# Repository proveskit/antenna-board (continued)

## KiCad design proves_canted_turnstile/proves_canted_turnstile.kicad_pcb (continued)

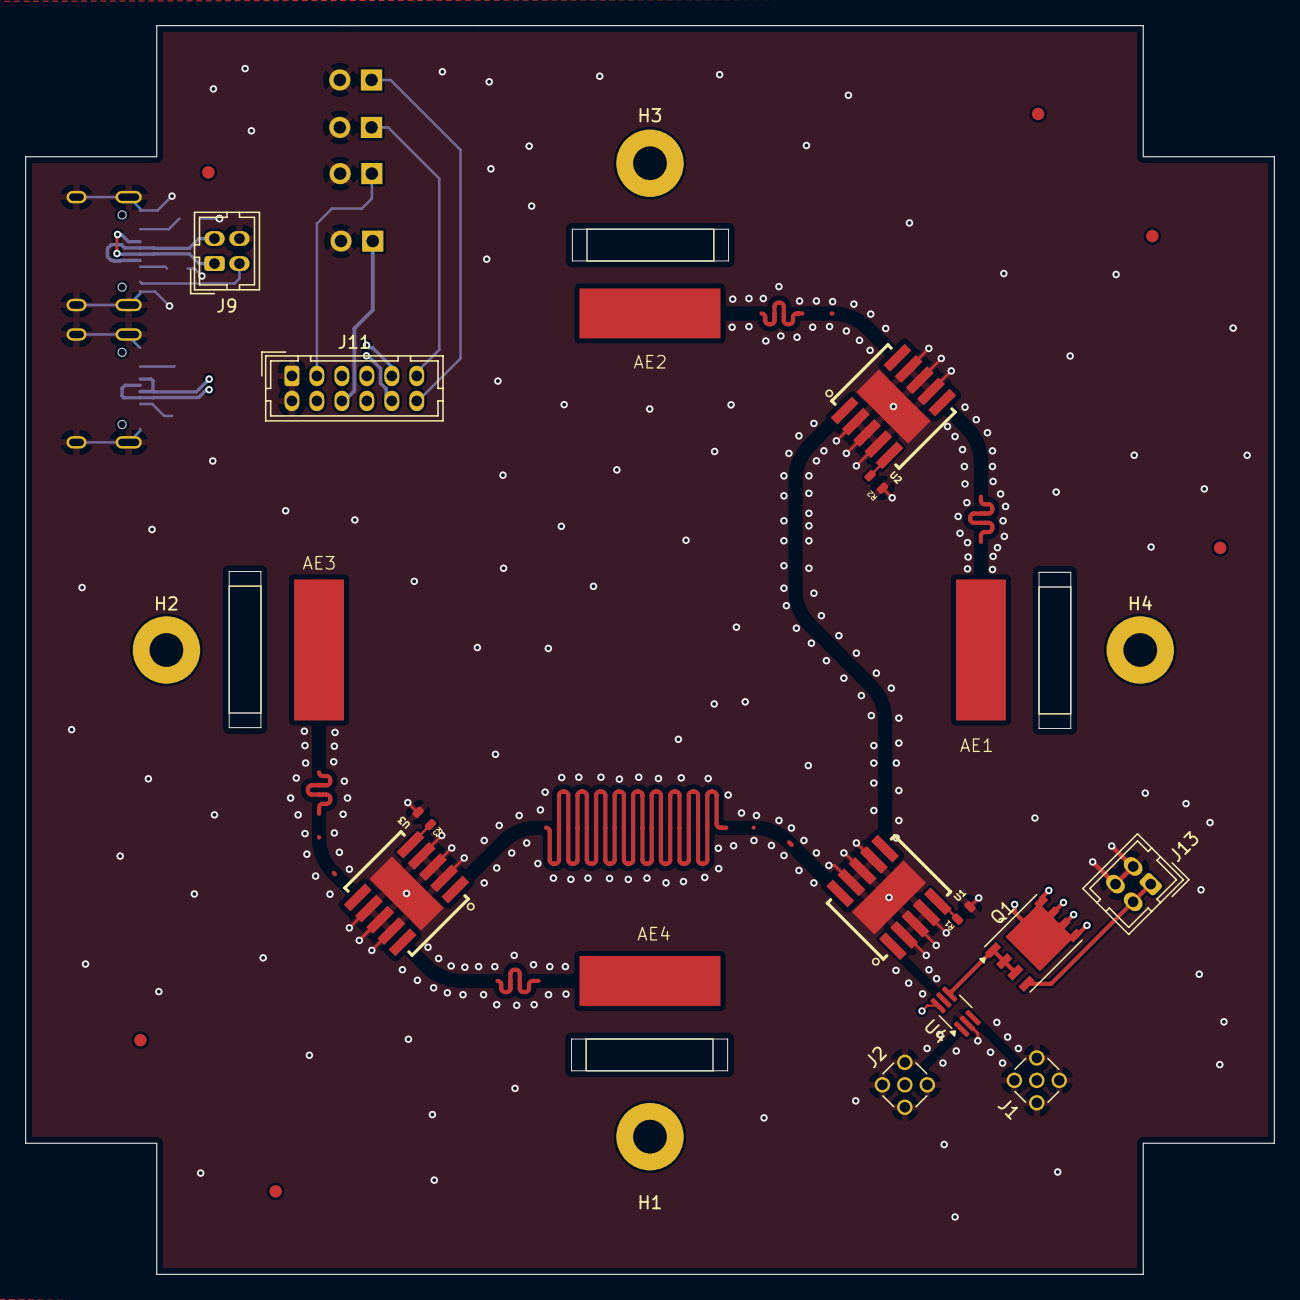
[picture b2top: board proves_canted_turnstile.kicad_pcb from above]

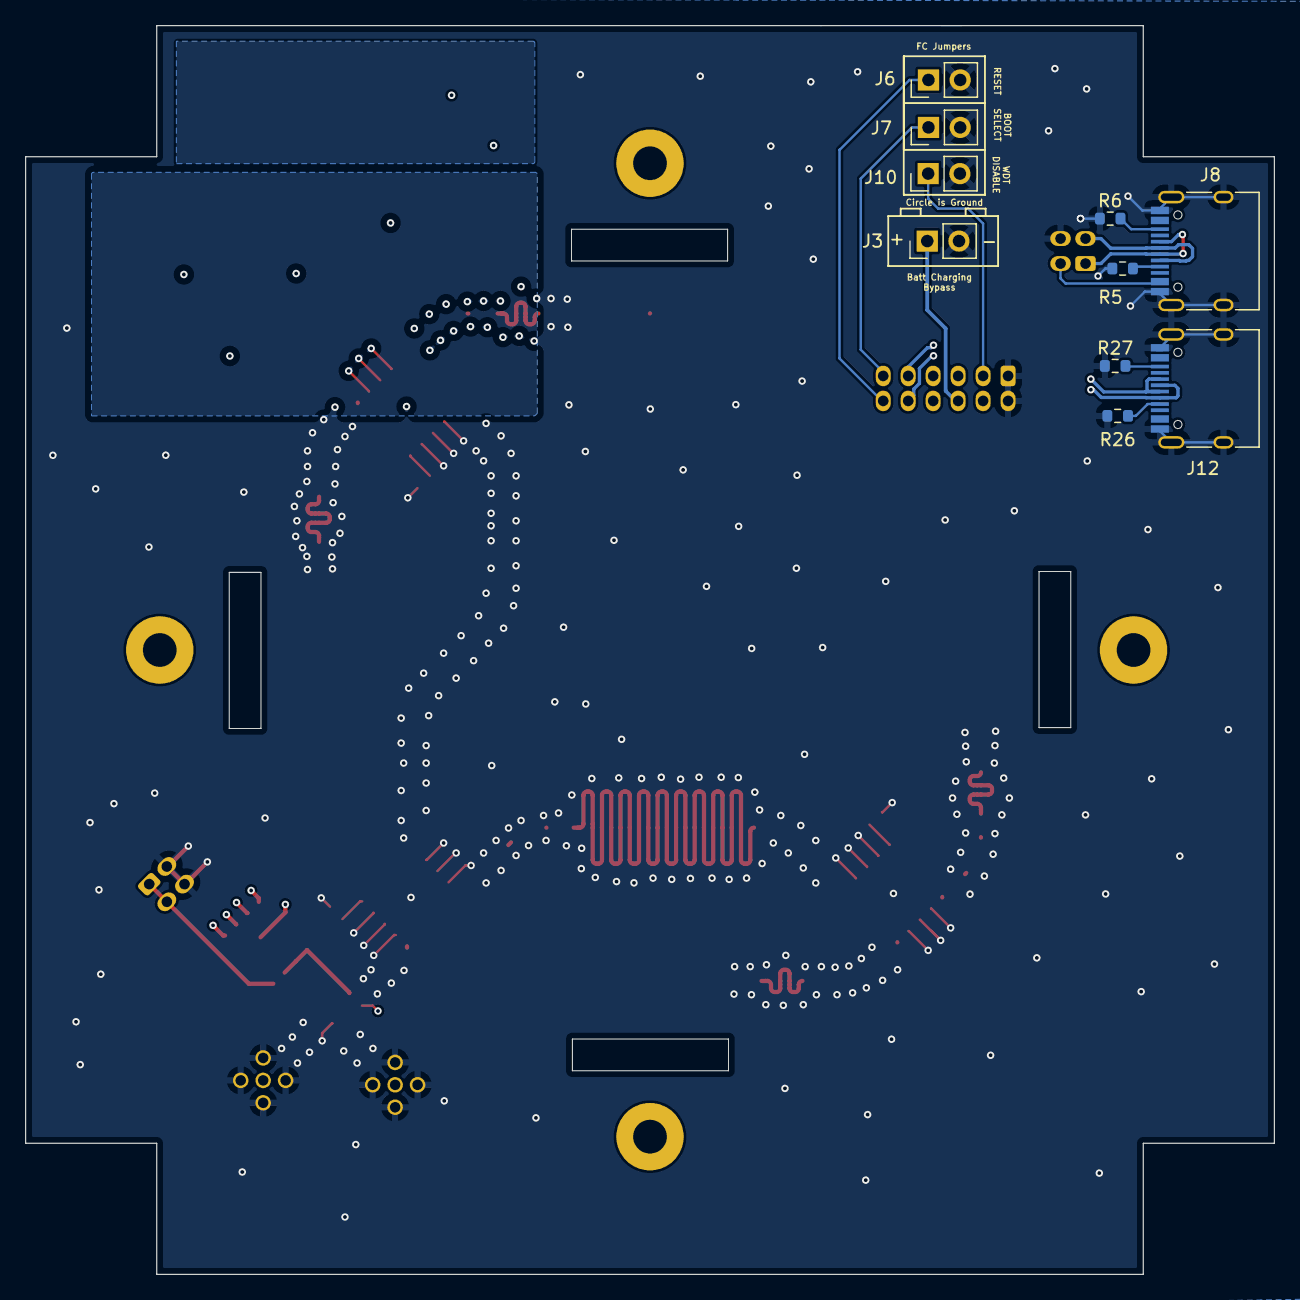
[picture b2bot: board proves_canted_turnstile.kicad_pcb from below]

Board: 4 copper layers, 100.0 x 100.0 mm, 37 parts (10 on the bottom side), 29 nets.

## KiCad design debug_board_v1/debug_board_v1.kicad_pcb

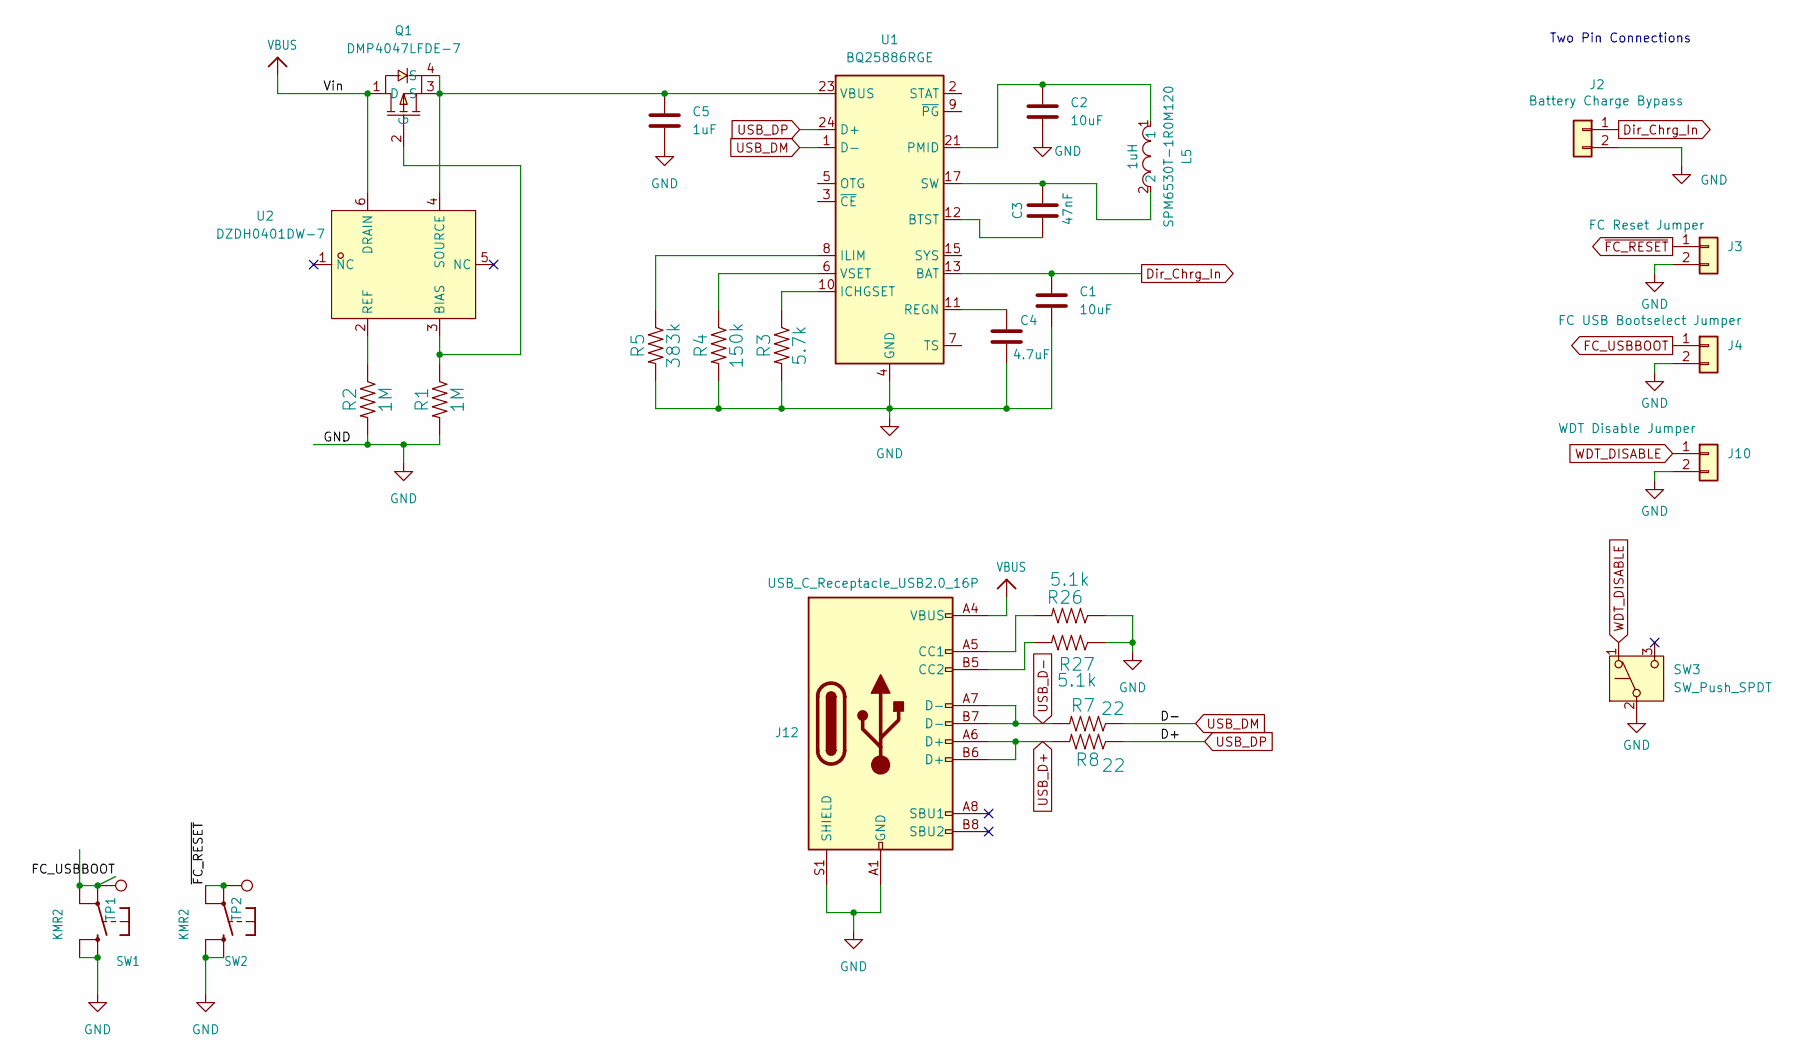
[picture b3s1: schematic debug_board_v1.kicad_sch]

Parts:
C1, C2: 10uF; C_0603_1608Metric
C3: 47nF; C_0603_1608Metric
C4: 4.7uF; C_0603_1608Metric
C5: 1uF; C_0603_1608Metric
J2: Battery Charge Bypass; PinHeader_1x02_P2.54mm_Vertical
J3: FC Reset Jumper; PinHeader_1x02_P2.54mm_Vertical
J4: FC USB Bootselect Jumper; PinHeader_1x02_P2.54mm_Vertical
J10: WDT Disable Jumper; PinHeader_1x02_P2.54mm_Vertical
J12: USB_C_Receptacle_USB2.0_16P; USB_C_Receptacle_HRO_TYPE-C-31-M-12
L5: SPM6530T-1R0M120; IND-SMD_L7.1-W6.5-P5.60; LCSC Part C87572
Q1: DMP4047LFDE-7; U-DFN2020-6E_L2.0-W2.0-P0.65-BL; LCSC Part C442635
R1, R2: 1M; R_0603_1608Metric
R3: 5.7k; R_0603_1608Metric
R4: 150k; R_0603_1608Metric
R5: 383k; R_0603_1608Metric
R7, R8: 22; R_0402_1005Metric
R26, R27: 5.1k; R_0603_1608Metric
SW1, SW2: KMR2; BTN_KMR2_4.6X2.8
SW3: SW_Push_SPDT; SW-TH_SHOU-HAN_SS12D10G4
TP1: USBBOOT; TestPoint_Loop_D1.80mm_Drill1.0mm_Beaded
TP2: RESET; TestPoint_Loop_D1.80mm_Drill1.0mm_Beaded
U1: BQ25886RGE; Texas_RGE0024H_VQFN-24-1EP_4x4mm_P0.5mm_EP2.7x2.7mm
U2: DZDH0401DW-7; SOT-363_L2.0-W1.3-P0.65-LS2.1-BR; LCSC Part C3235552

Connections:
Dir_Chrg_In: C1.1, J2.1, U1.13 (BAT), U1.14 (BAT)
FC_USBBOOT: J4.1, SW1.A, SW1.A' (P1), TP1.1
GND: C1.2, C2.2, C4.2, C5.2, J2.2, J3.2, J4.2, J10.2, J12.A1 (GND), J12.A12 (GND), J12.B1 (GND), J12.B12 (GND), J12.S1 (SHIELD), R1.2, R2.2, R3.2, R4.2, R5.2, R26.1, R27.1, SW1.B (S), SW1.B' (S1), SW2.B (S), SW2.B' (S1), SW3.2 (B), U1.4 (GND), U1.19 (GND), U1.20 (GND), U1.25 (GND)
unnamed: C2.1, L5.1, U1.21 (PMID), U1.22 (PMID)
unnamed: C3.2, L5.2, U1.17 (SW), U1.18 (SW)
unnamed: J12.A5 (CC1), R26.2
unnamed: J12.B5 (CC2), R27.2
unnamed: Q1.2 (G), R1.1, U2.3 (BIAS)
unnamed: C3.1, U1.12 (BTST)
unnamed: R3.1, U1.10 (ICHGSET)
unnamed: R5.1, U1.8 (ILIM)
unnamed: C4.1, U1.11 (REGN)
unnamed: U1.15 (SYS), U1.16 (SYS)
unnamed: C5.1, Q1.3 (S), Q1.4 (S), U1.23 (VBUS), U2.4 (SOURCE)
unnamed: R4.1, U1.6 (VSET)
unnamed: R2.1, U2.2 (REF)
USB_D+: J12.A6 (D+), J12.B6 (D+), R8.2
USB_D-: J12.A7 (D-), J12.B7 (D-), R7.2
USB_DM: R7.1, U1.1 (D-)
USB_DP: R8.1, U1.24 (D+)
VBUS: J12.A4 (VBUS), J12.A9 (VBUS), J12.B4 (VBUS), J12.B9 (VBUS), Q1.1 (D), U2.6 (DRAIN)
WDT_DISABLE: J10.1, SW3.1 (A)
~FC_RESET: J3.1, SW2.A, SW2.A' (P1), TP2.1

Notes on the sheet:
Two Pin Connections

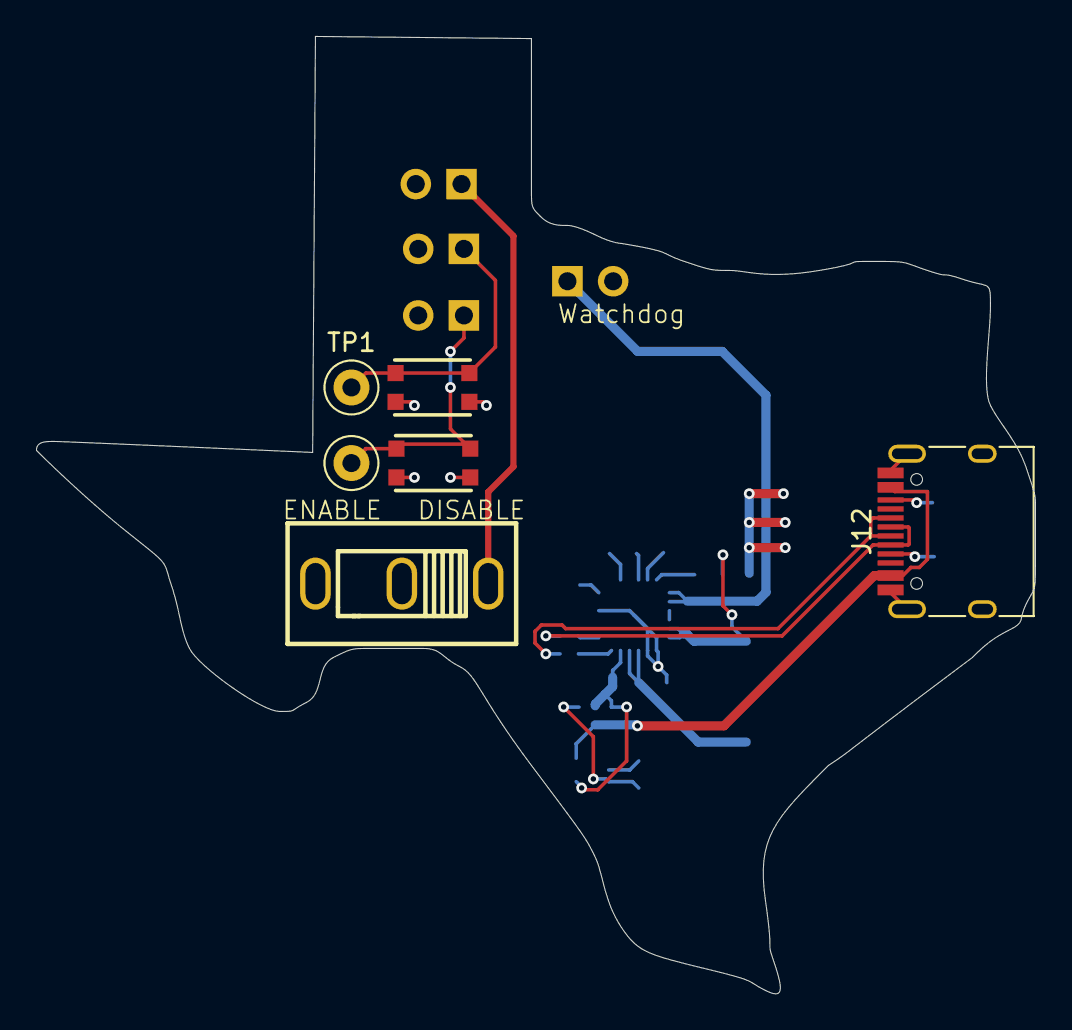
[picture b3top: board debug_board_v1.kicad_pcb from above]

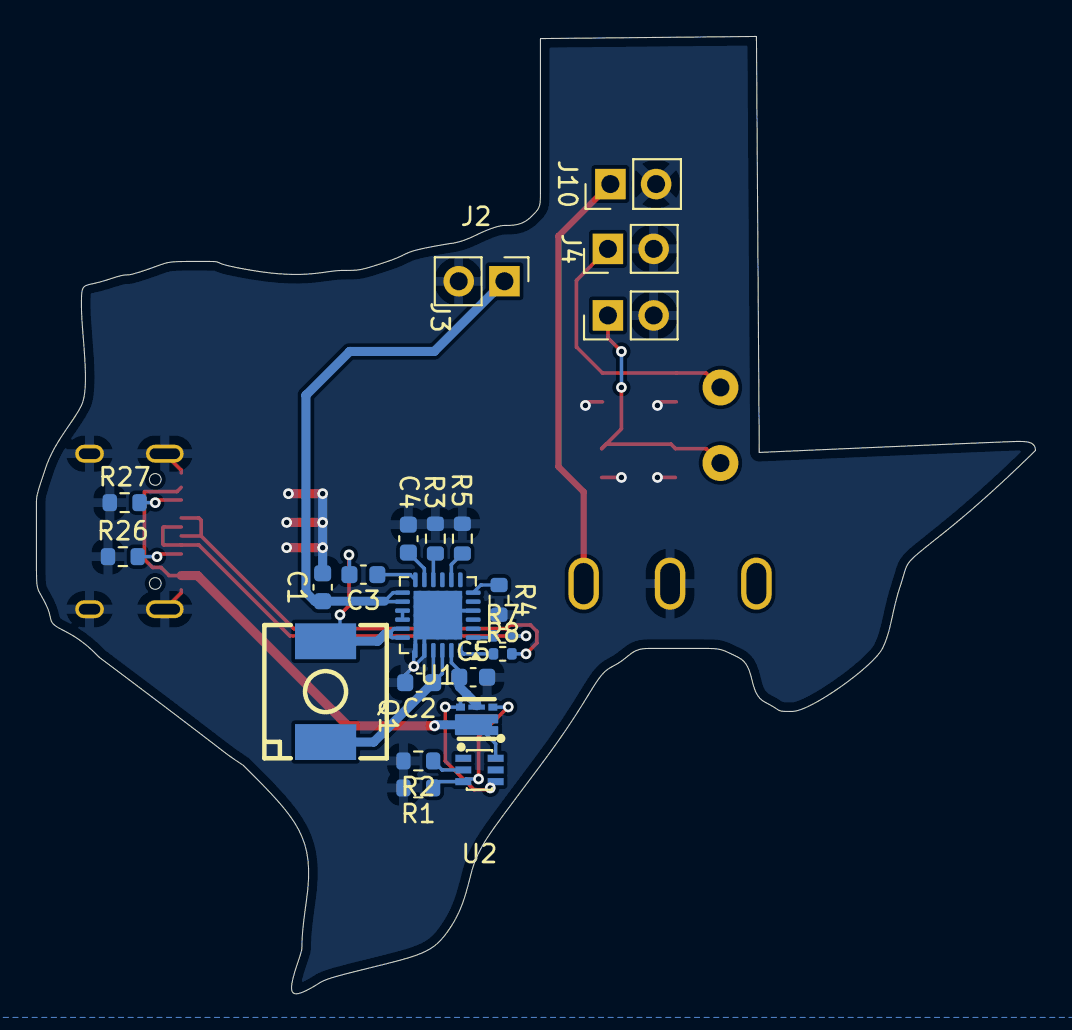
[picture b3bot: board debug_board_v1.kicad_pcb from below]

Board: 2 copper layers, 55.5 x 53.2 mm, 28 parts (22 on the bottom side), 23 nets.

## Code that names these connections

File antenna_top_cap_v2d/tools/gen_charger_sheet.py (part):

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gnd(JC.p("SH"))
vin = (71.12, P["23"][1])
wire(JC.p("A4"), (71.12, JC.p("A4")[1]), (71.12, 58.42), vin)
label("VBUS_CHG", vin)
for pin, x, ref in (("A5", 60.96, "R208"), ("B5", 50.8, "R209")):
    wire(JC.p(pin), (x, JC.p(pin)[1]))
    t, b = res(ref, "5.1k", x, JC.p(pin)[1], "C23186", "CC pull-down Rd: USB-C sink, 5 V only")
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
# Right side pins get short stubs to named nets.
noconnect(P["9"])
for pin, name in [("2", "CHG_STAT"), ("21", "PMID"), ("17", "SW"), ("12", "BTST"),
                  ("15", "SYS"), ("13", "CHG_BAT"), ("11", "REGN"), ("7", "TS")]:
    end = (P[pin][0] + 7.62, P[pin][1])
    wire(P[pin], end)
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# ---------------------------------------------------------------- power stage
# PMID bus: C202/C203, then L201 to SW.
yb = 50.8
label("PMID", (134.62, yb))
wire((134.62, yb), (139.7, yb), (160.02, yb))
junction((139.7, yb))
cap("C202", "22uF", 139.7, yb, "C45783", "PMID input cap, 25 V X5R (VBUS + PMID >= 10 uF after derating)")
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
# Bootstrap cap BTST to SW.
yt = 63.5
label("BTST", (172.72, yt))
Cb = Sym("Device:C", "C208", "47nF", 182.88, yt, rot=90, fp=C0603, lcsc="C1622", desc="Bootstrap cap",
         ref_at=(181.61, yt - 5.08), val_at=(181.61, yt - 2.54))
a, b = sorted([Cb.p(1), Cb.p(2)])
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
# SYS (boost output): 3 x 22uF.
ys = 76.2
label("SYS", (134.62, ys))
wire((134.62, ys), (139.7, ys), (149.86, ys), (160.02, ys))
for i, x in enumerate([139.7, 149.86, 160.02]):
    if x != 160.02:
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
# BAT: C207, F201, CHG LINK R210 (0 Ohm) to the battery tap.
ybat = 101.6
label("CHG_BAT", (134.62, ybat))
wire((134.62, ybat), (139.7, ybat), (144.78, ybat))
junction((139.7, ybat))
cap("C207", "22uF", 139.7, ybat, "C12891", "BAT cap, 25 V X5R 1206: about 14 uF at 8.2 V (>= 10 uF)", fp=C1206)
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fa, fb = sorted([F.p(1), F.p(2)])
wire((144.78, ybat), fa)
wire(fb, (154.94, ybat))
label("CHG_FUSED", (154.94, ybat))
RL = Sym("Device:R", "R210", "0", 162.56, ybat, rot=90, fp="Resistor_SMD:R_1206_3216Metric", lcsc="C17888",
         desc="CHG LINK: 0 Ohm on the outer face; hot-air it off before handoff (remove before flight)",
         ref_at=(160.02, ybat - 3.81), val_at=(160.02, ybat - 6.35))
ra, rb = sorted([RL.p(1), RL.p(2)])
wire((154.94, ybat), ra)
wire(rb, (172.72, ybat))
hlabel("Dir_Chrg_In", (172.72, ybat), "passive", rot=0)
text("CHG LINK (remove before flight)", 156.21, ybat + 3.81)

# REGN: C209, TS divider, status LEDs.
yr = 121.92
label("REGN", (134.62, yr))
wire((134.62, yr), (139.7, yr), (149.86, yr), (180.34, yr))
junction((139.7, yr))
cap("C209", "4.7uF", 139.7, yr, "C19666", "REGN bypass", fp=C0603)
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junction(b)
wire(b, (157.48, b[1]))
label("TS", (157.48, b[1]))
label("VBUS_CHG", (167.64, yr - 7.62))
for x, ytop, rref, dref, col, net, dlcsc, dfp, rdesc in [
    (167.64, yr - 7.62, "R206", "D201", "Green", None, "C2297", "LED_SMD:LED_0805_2012Metric", "USB 5 V present: (5 - 2.8) / 4.7k = 0.5 mA; 85 mW at a 20 V fault"),
    (180.34, yr, "R207", "D202", "Red", "CHG_STAT", "C2286", "LED_SMD:LED_0603_1608Metric", "STAT LED: (REGN - 2) / 2.2k = 1.4 mA"),
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     "VBUS operating 4.3 to 6.2 V, OVP 6.2 V, abs max 20 V. VINDPM 4.3 V backs the charger off on a weak port.\n"
     "IINDPM = KILIM / RILIM = 1110 / 820 = 1.35 A (Type-C 1.5 A level). ICHG = 3.9k / 3810 = 1.02 A max; at 1.35 A in, about 0.75 A reaches the pack.\n"
     "VBUS = (4.3, 5.0, 6.2) V @ (0, 1.2, 1.35) A. CHG_BAT = (6.0, 7.4, 8.2) V @ (0, 0.7, 1.02) A.\n"
     "ICHG stays at or under 1.02 A: Dir_Chrg_In reaches the FC on one 24 AWG harness conductor (J1 pin 6).", 25.4, 27.94)
text("D+ tied to D-: BC1.2 detects a DCP (3 A), so ILIM governs.\n"
     "J204 data pins are not connected (charge only).", 25.4, 90.17)
text("OTG and ~{CE} hard tied to GND.\n"
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
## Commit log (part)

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2025-09-26 V2b: Switched From VEML7700 to VEML61
2025-10-08 Added Turnstile Board
2025-10-08 As ORdered For V3 Pro
2025-10-08 Design Corrections for Ordering
    - Adjusted solder mask clearance
    - Changed trace width for JLC stackup
2026-03-05 Created Maia Project
2026-03-27 updated file name and added new edge cut
2026-03-27 deleted duplicate files
2026-03-27 restarted and created new project files for proves version of canted turnstile antenna
2026-03-27 transferred schematic and symbols
2026-03-27 assigned footprints to symbols and imported fiducials
2026-03-27 imported footprints
2026-03-27 made copper zones
2026-03-29 implemented burnwire in schematic
2026-03-30 added tape measure slot footprint
2026-03-31 changed trace widths
2026-03-31 tuned lengths of U3 to 180 and 270 degree pads
2026-03-31 finished critical traces
2026-03-31 placement of fiducials
2026-03-31 placed mounting holes
2026-03-31 placed mounting holes
    have to readjust the pads now : (
2026-03-31 updated pad positions for antenna elements
2026-04-01 porting proves features
2026-04-01 Finished board
2026-04-01 adjusted antenna landing pads
2026-04-01 adjusted traces and updates
2026-04-01 changed burnwire resistor position
2026-04-01 updated impedance of rf traces to be single ended coplanar
2026-04-01 updated 90 degree phase shift trace length
2026-04-07 More Debug Board Work!
2026-04-07 Production File Updates
2026-05-14 implemented RF Switch
2026-05-14 updated usb differential pair track widths
2026-05-15 fixed net labels
2026-05-17 removed burnwire resistor and fixed up some traces
2026-05-18 gerber files and minor modifications
